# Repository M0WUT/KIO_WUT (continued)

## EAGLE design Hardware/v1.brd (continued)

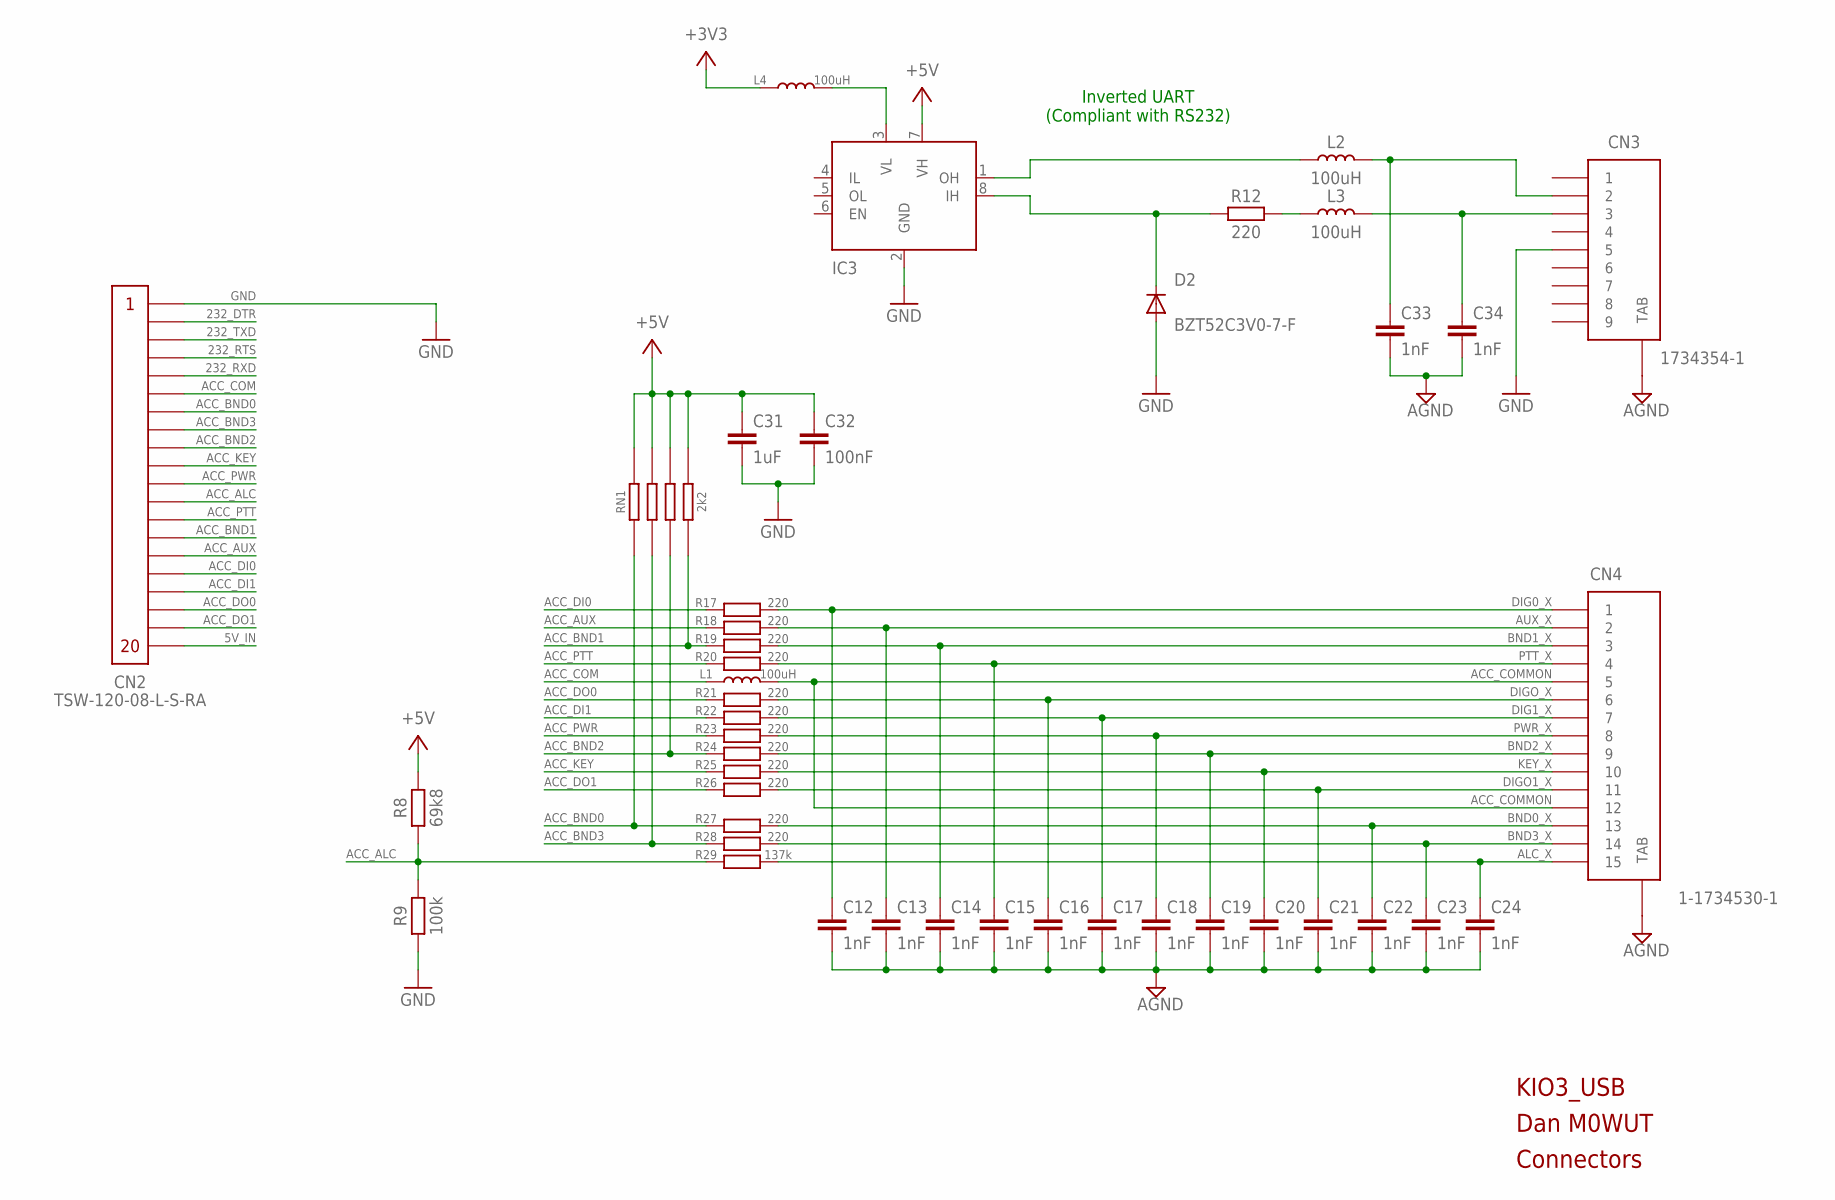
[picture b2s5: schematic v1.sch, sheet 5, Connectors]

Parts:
C12, C13, C14, C15, C16, C17, C18, C19, C20, C21, C22, C23, C24, C33, C34: 1nF; C0402
C31: 1uF; C0402
C32: 100nF; C0402
CN2: TSW-120-08-L-S-RA; CONN_0.1_1X20
CN3: 1734354-1; CONN_TE_DE9
CN4: 1-1734530-1; CONN_TE_DE-HD15
D2: BZT52C3V0-7-F; SOD-123
IC3: IC_MAX3375; SOT23-8L
L1, L2, L3, L4: 100uH; R0805
R8: 69k8; R0402
R9: 100k; R0402
R12: 220; R0402
R17, R18, R19, R20, R21, R22, R23, R24, R25, R26, R27, R28: 220; R0805
R29: 137k; R0805
RN1: 2k2; R_BOURNS_CAY16-J4

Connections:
5V_IN: CN2.P$20
232_DTR: CN2.P$2
232_RTS: CN2.P$4
232_RXD: CN2.P$5
232_TXD: CN2.P$3
+3V3: L4.1; also elsewhere on the board
+5V: C31.1, C32.1, IC3.7 (VH), R8.2, RN1.1, RN1.2, RN1.3, RN1.4; also elsewhere on the board
ACC_ALC: CN2.P$12, R8.1, R9.2, R29.1
ACC_AUX: CN2.P$15, R18.1
ACC_BND0: CN2.P$7, R27.1, RN1.1A
ACC_BND1: CN2.P$14, R19.1, RN1.4A
ACC_BND2: CN2.P$9, R24.1, RN1.3A
ACC_BND3: CN2.P$8, R28.1, RN1.2A
ACC_COM: CN2.P$6, L1.1
ACC_COMMON: CN4.5, CN4.12, L1.2
ACC_DI0: CN2.P$16, R17.1
ACC_DI1: CN2.P$17, R22.1
ACC_DO0: CN2.P$18, R21.1
ACC_DO1: CN2.P$19, R26.1
ACC_KEY: CN2.P$10, R25.1
ACC_PTT: CN2.P$13, R20.1
ACC_PWR: CN2.P$11, R23.1
AGND: C12.2, C13.2, C14.2, C15.2, C16.2, C17.2, C18.2, C19.2, C20.2, C21.2, C22.2, C23.2, C24.2, C33.2, C34.2, CN3.TAB, CN3.TAB1 (TAB), CN4.16 (TAB), CN4.17 (TAB); also elsewhere on the board
ALC_X: C24.1, CN4.15, R29.2
AUX_X: C13.1, CN4.2, R18.2
BND0_X: C22.1, CN4.13, R27.2
BND1_X: C14.1, CN4.3, R19.2
BND2_X: C19.1, CN4.9, R24.2
BND3_X: C23.1, CN4.14, R28.2
DIG0_X: C12.1, CN4.1, R17.2
DIG1_X: C17.1, CN4.7, R22.2
DIGO1_X: C21.1, CN4.11, R26.2
DIGO_X: C16.1, CN4.6, R21.2
GND: C31.2, C32.2, CN2.P$1, CN3.5, D2.A, IC3.2 (GND), R9.1; also elsewhere on the board
KEY_X: C20.1, CN4.10, R25.2
unnamed: C34.1, CN3.3, L3.2
unnamed: L3.1, R12.2
unnamed: IC3.3 (VL), L4.2
unnamed: C33.1, CN3.2, L2.2
unnamed: IC3.1 (OH), L2.1
unnamed: D2.C, IC3.8 (IH), R12.1
PTT_X: C15.1, CN4.4, R20.2
PWR_X: C18.1, CN4.8, R23.2

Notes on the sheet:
KIO3_USB
Dan M0WUT
Connectors
Inverted UART (Compliant with RS232)

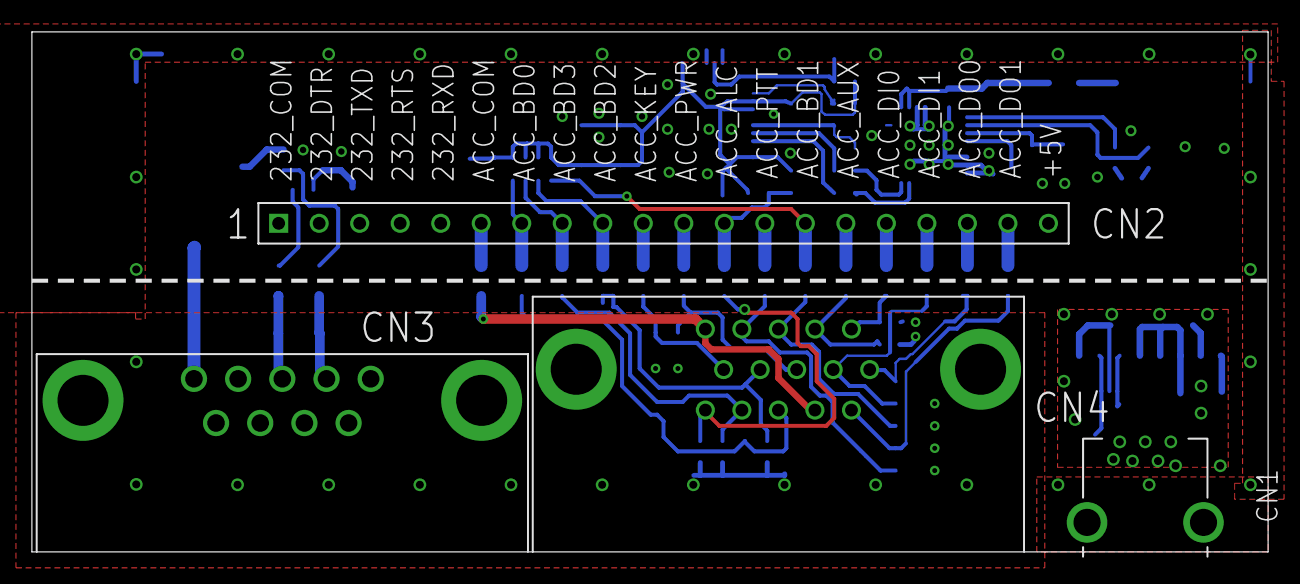
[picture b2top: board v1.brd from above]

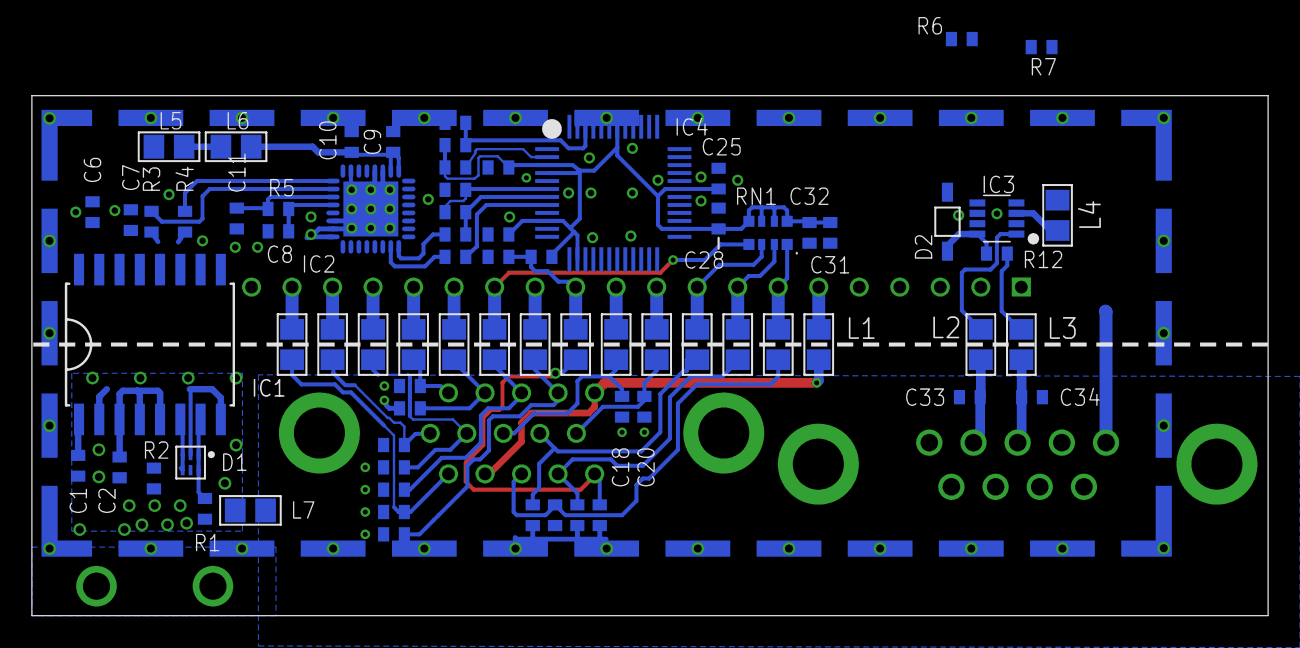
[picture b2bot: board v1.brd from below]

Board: 2 copper layers, 77.5 x 32.6 mm, 78 parts (74 on the bottom side), 61 nets.

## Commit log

2018-10-08 added ft2232
2018-10-18 added eeprom and expanded sch
2018-10-31 Resized PCB now I have reference board
2018-11-04 finished input side of usb isolator
2018-11-05 most of usb hub implemented
2018-11-11 mirrored digital section of board to allow for easier routing to io
2018-11-27 finally got the decoupling caps for the db15 to fit
2018-11-29 reorganised decoupling caps to be slightly less crazy
2018-12-01 fixed some silkscreen issues
2018-12-01 added missing pullups to band lines
2018-12-02 complete apart from sound card and PIC
2018-12-12 destruction in the name of progress...
2019-01-07 nearly there...
2019-01-24 Initial changes from v1 + started code
2019-01-27 Started work but fighting Microchip's stupid library
2019-01-28 it lives!!!
2019-01-29 All 4 UARTS TXing
2019-01-29 removed stuff leftover from debugging
2019-01-31 loopback tests working
2019-01-31 updated gitignore to (hopefully) remove junk
2019-01-31 messing with git ignore
2019-01-31 Removed all of the junk files
2019-02-01 All the forwarding between devices working :)
2019-02-02 all done, now for testing with K3
2019-02-13 Implementing Board changes from v1
2019-02-18 v2 pcb ordered
2019-02-18 Update with a change that I wish was in v2
2019-03-07 renumbered parts, minor BOM update
2019-03-14 minor code fixes
2021-06-12 testing branching worked as planned
2021-06-12 Added kicad project
2021-06-14 more layout work
